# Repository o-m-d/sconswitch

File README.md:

# Serial Controlled Switch

## Device description
Device have 32 high voltage open collector outputs, controlled by commands
via RS-232 port. Outputs can be in active or passive state and can drive
relays, solenoids, LEDs, opto triacs etc.
Active state - output transistor open, passive state - output transistor
closed.

Device can be used in power control, lighting or any other suitable
applications.

Device connects to controlled system via 40-wire ribbon cable and to
controlling host via DE9 connector.

Device IS NOT realtime and may not used in time-sensitive applications,
e.g. CNC.

Device built on microcontroller ATmega8515-16 in TQFP44 package and
drivers ULN2803A in SOIC-18 package.

In firmware part used [KonstantinChizhov/Mcucpp library] (https://github.com/KonstantinChizhov/Mcucpp)
and [Peter Fleury UART library] (http://homepage.hispeed.ch/peterfleury/avr-software.html).
Firmware compiled by avr-gcc-4.8, pcb designed in KiCAD-4.0.1.

## Supported commands
<pre>
a N|a   - Active output number N (or all)
p N|a   - Passive output number N (or all)
t N D   - Toggle output N for D (1-255) seconds, press s for stop during 
          countdown
n NAME  - Output name, set to NAME or unset if empty given
s       - Show output status
h or ?  - Show this help
</pre>

Output status saved automatically to EEPROM with Active or Passive commands
and restored when power-up.
Commands are not case sensitive. Command line are not editable.

Outputs have numbers from 0 to 31. Toggle means temporary inversion of
output state.

[Demo video](https://youtu.be/6nN7ayRqDR0)

## Electrical characteristics
<pre>
Supply voltage: 9-15V
Supply current: 25mA at 10V
Max voltage on closed output: 50V
Max current via one open output: 500mA
Max total current via all open outputs: 4A (125mA per output and 2x2A per
two ground wires in ribbon cable)
</pre>

Characteristics depend on applied components.

## RS-232 mode
9600 8N1

## Design Recommendations
* Use short as possible ribbon cable.
* Use only 40-wire ribbon cable, not 80-wire UDMA cable.
* ULN2803 have built-in surge protection diodes for inductive load, but
better use discrete diodes, placed as close as possible to coil.

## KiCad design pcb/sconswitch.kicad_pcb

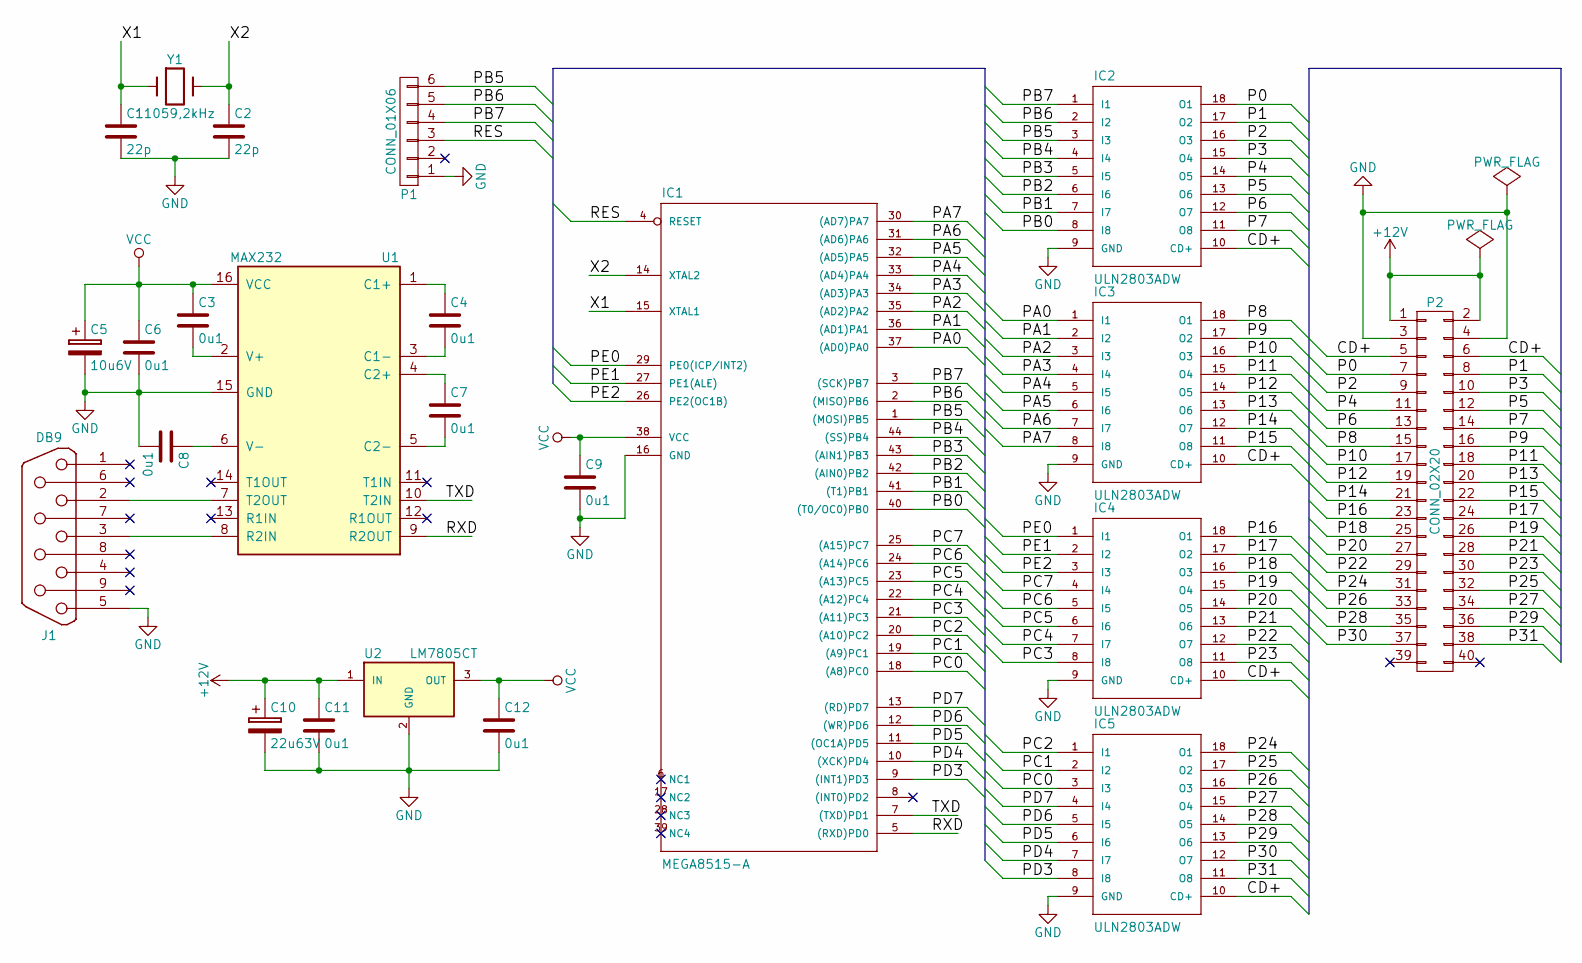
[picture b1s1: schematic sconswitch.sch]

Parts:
C1, C2: 22p; C_0603
C3, C4, C6, C7, C8, C9, C11, C12: 0u1; C_0603
C5: 10u6V; C_Radial_D5_L6_P2.5
C10: 22u63V; C_Radial_D10_L13_P5
IC1: MEGA8515-A; TQFP-44_10x10mm_Pitch0.8mm
IC2, IC3, IC4, IC5: ULN2803ADW; SOIC-18_7.5x11.6mm_Pitch1.27mm
J1: DB9; DB9FC
P1: CONN_01X06; Pin_Header_Straight_1x06
P2: CONN_02X20; Pin_Header_Straight_2x20
U1: MAX232; SO-16-N
U2: LM7805CT; TO-220_Horizontal_LargePads
Y1: 11059,2kHz; Crystal_HC49-U_Horizontal_Typ1

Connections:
+12V: C10.1, C11.1, P2.1, P2.2, U2.1 (IN)
/CD+: IC2.10 (CD+), IC3.10 (CD+), IC4.10 (CD+), IC5.10 (CD+), P2.5, P2.6
/P0: IC2.18 (O1), P2.7
/P1: IC2.17 (O2), P2.8
/P2: IC2.16 (O3), P2.9
/P3: IC2.15 (O4), P2.10
/P4: IC2.14 (O5), P2.11
/P5: IC2.13 (O6), P2.12
/P6: IC2.12 (O7), P2.13
/P7: IC2.11 (O8), P2.14
/P8: IC3.18 (O1), P2.15
/P9: IC3.17 (O2), P2.16
/P10: IC3.16 (O3), P2.17
/P11: IC3.15 (O4), P2.18
/P12: IC3.14 (O5), P2.19
/P13: IC3.13 (O6), P2.20
/P14: IC3.12 (O7), P2.21
/P15: IC3.11 (O8), P2.22
/P16: IC4.18 (O1), P2.23
/P17: IC4.17 (O2), P2.24
/P18: IC4.16 (O3), P2.25
/P19: IC4.15 (O4), P2.26
/P20: IC4.14 (O5), P2.27
/P21: IC4.13 (O6), P2.28
/P22: IC4.12 (O7), P2.29
/P23: IC4.11 (O8), P2.30
/P24: IC5.18 (O1), P2.31
/P25: IC5.17 (O2), P2.32
/P26: IC5.16 (O3), P2.33
/P27: IC5.15 (O4), P2.34
/P28: IC5.14 (O5), P2.35
/P29: IC5.13 (O6), P2.36
/P30: IC5.12 (O7), P2.37
/P31: IC5.11 (O8), P2.38
/PA0: IC1.37 ((AD0)PA0), IC3.1 (I1)
/PA1: IC1.36 ((AD1)PA1), IC3.2 (I2)
/PA2: IC1.35 ((AD2)PA2), IC3.3 (I3)
/PA3: IC1.34 ((AD3)PA3), IC3.4 (I4)
/PA4: IC1.33 ((AD4)PA4), IC3.5 (I5)
/PA5: IC1.32 ((AD5)PA5), IC3.6 (I6)
/PA6: IC1.31 ((AD6)PA6), IC3.7 (I7)
/PA7: IC1.30 ((AD7)PA7), IC3.8 (I8)
/PB0: IC1.40 ((T0/OC0)PB0), IC2.8 (I8)
/PB1: IC1.41 ((T1)PB1), IC2.7 (I7)
/PB2: IC1.42 ((AIN0)PB2), IC2.6 (I6)
/PB3: IC1.43 ((AIN1)PB3), IC2.5 (I5)
/PB4: IC1.44 ((SS)PB4), IC2.4 (I4)
/PB5: IC1.1 ((MOSI)PB5), IC2.3 (I3), P1.6
/PB6: IC1.2 ((MISO)PB6), IC2.2 (I2), P1.5
/PB7: IC1.3 ((SCK)PB7), IC2.1 (I1), P1.4
/PC0: IC1.18 ((A8)PC0), IC5.3 (I3)
/PC1: IC1.19 ((A9)PC1), IC5.2 (I2)
/PC2: IC1.20 ((A10)PC2), IC5.1 (I1)
/PC3: IC1.21 ((A11)PC3), IC4.8 (I8)
/PC4: IC1.22 ((A12)PC4), IC4.7 (I7)
/PC5: IC1.23 ((A13)PC5), IC4.6 (I6)
/PC6: IC1.24 ((A14)PC6), IC4.5 (I5)
/PC7: IC1.25 ((A15)PC7), IC4.4 (I4)
/PD3: IC1.9 ((INT1)PD3), IC5.8 (I8)
/PD4: IC1.10 ((XCK)PD4), IC5.7 (I7)
/PD5: IC1.11 ((OC1A)PD5), IC5.6 (I6)
/PD6: IC1.12 ((WR)PD6), IC5.5 (I5)
/PD7: IC1.13 ((RD)PD7), IC5.4 (I4)
/PE0: IC1.29 (PE0(ICP/INT2)), IC4.1 (I1)
/PE1: IC1.27 (PE1(ALE)), IC4.2 (I2)
/PE2: IC1.26 (PE2(OC1B)), IC4.3 (I3)
/RES: IC1.4 (RESET), P1.3
/RXD: IC1.5 ((RXD)PD0), U1.9 (R2OUT)
/TXD: IC1.7 ((TXD)PD1), U1.10 (T2IN)
/X1: C1.1, IC1.15 (XTAL1), Y1.1
/X2: C2.1, IC1.14 (XTAL2), Y1.2
GND: C1.2, C2.2, C5.2, C6.2, C8.2, C9.2, C10.2, C11.2, C12.2, IC1.16 (GND), IC2.9 (GND), IC3.9 (GND), IC4.9 (GND), IC5.9 (GND), J1.5, P1.1, P2.3, P2.4, U1.15 (GND), U2.2 (GND)
unnamed: C3.2, U1.2 (V+)
unnamed: C4.1, U1.1 (C1+)
unnamed: C4.2, U1.3 (C1-)
unnamed: C7.1, U1.4 (C2+)
unnamed: C7.2, U1.5 (C2-)
unnamed: C8.1, U1.6 (V-)
unnamed: J1.2, U1.7 (T2OUT)
unnamed: J1.3, U1.8 (R2IN)
VCC: C3.1, C5.1, C6.1, C9.1, C12.1, IC1.38 (VCC), U1.16 (VCC), U2.3 (OUT)

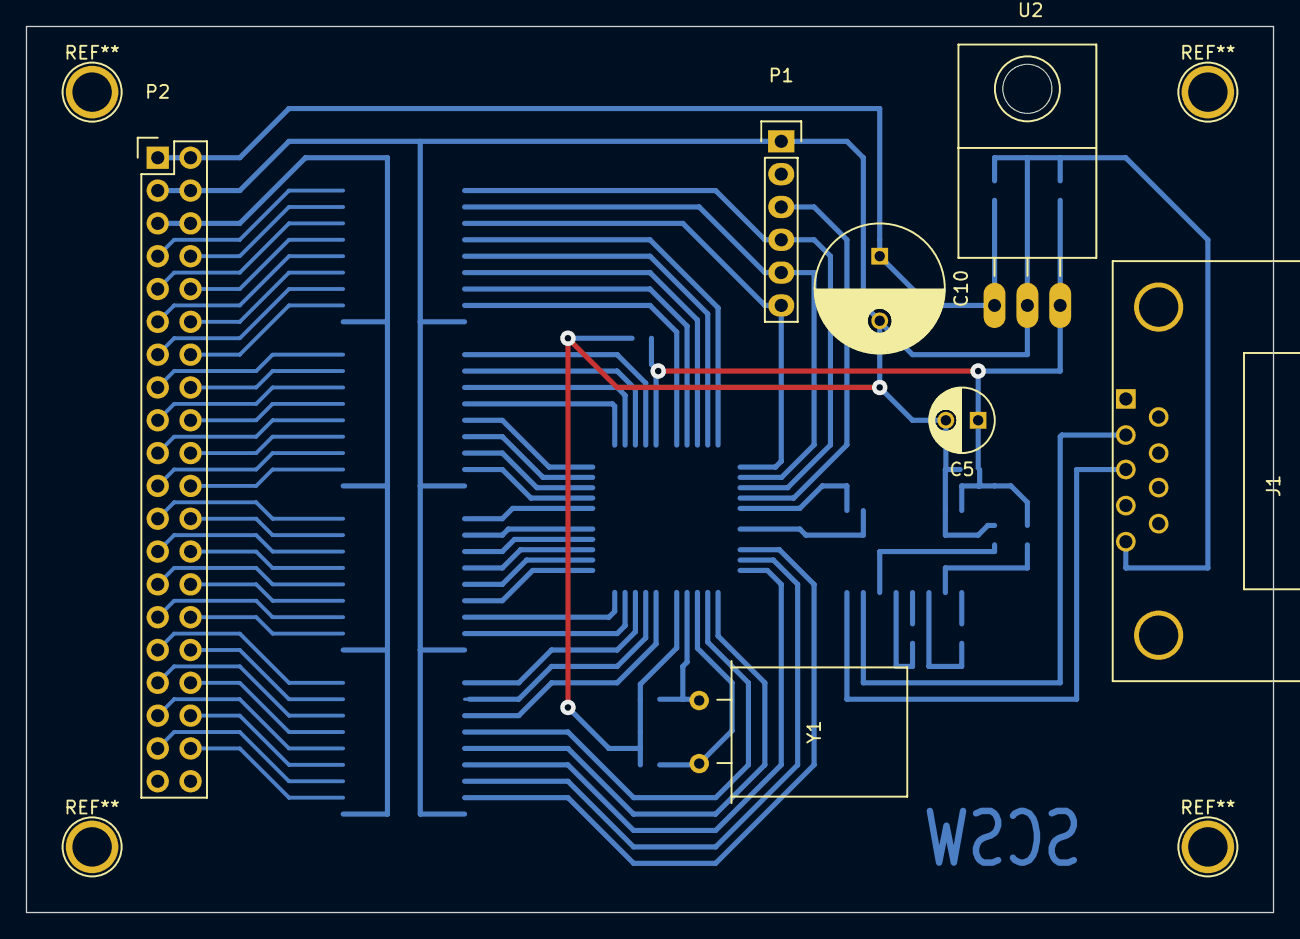
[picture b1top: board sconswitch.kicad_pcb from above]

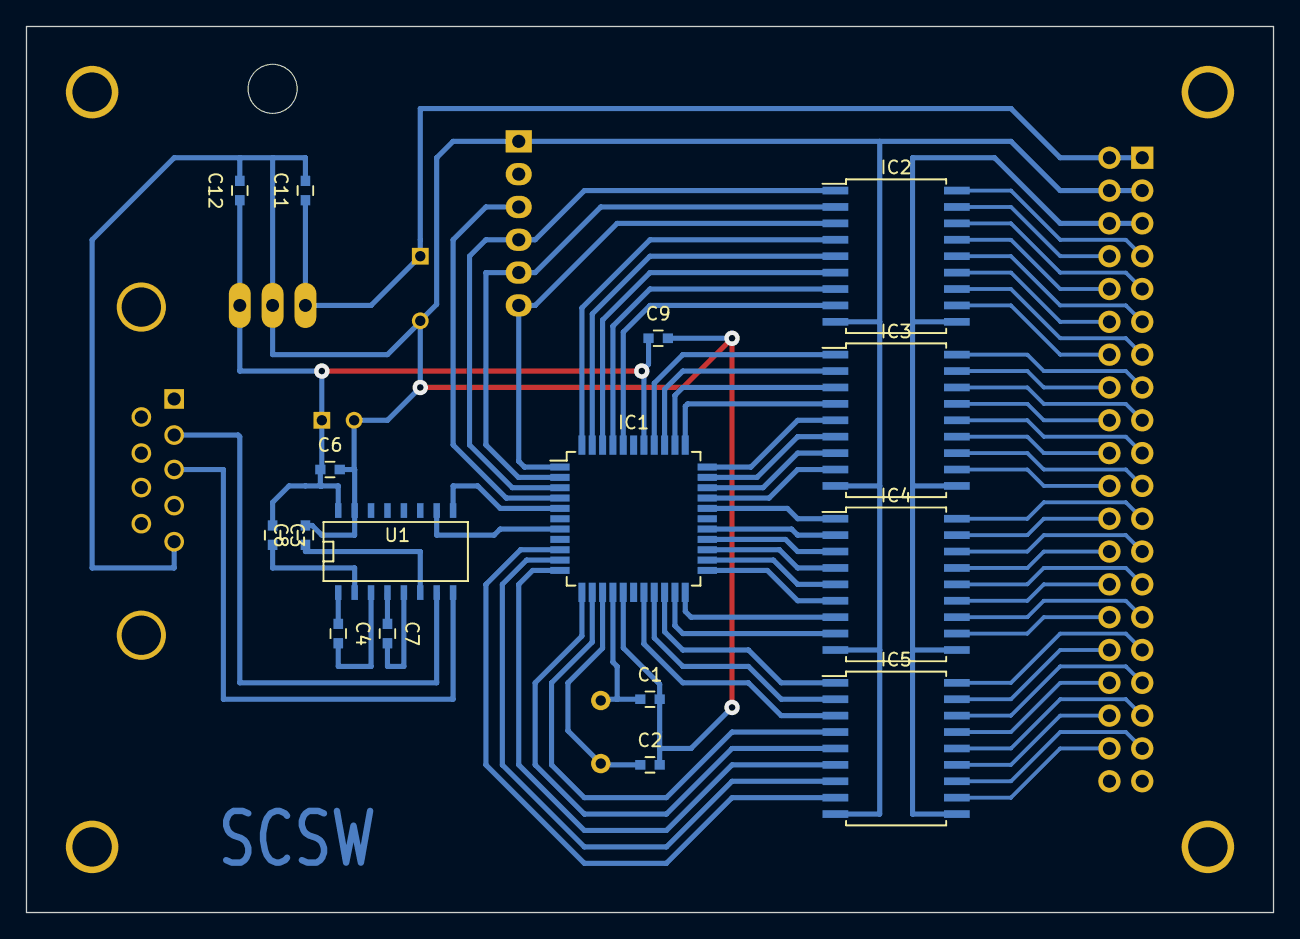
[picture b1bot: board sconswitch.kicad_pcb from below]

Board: 2 copper layers, 96.5 x 68.6 mm, 23 parts (16 on the bottom side), 81 nets.

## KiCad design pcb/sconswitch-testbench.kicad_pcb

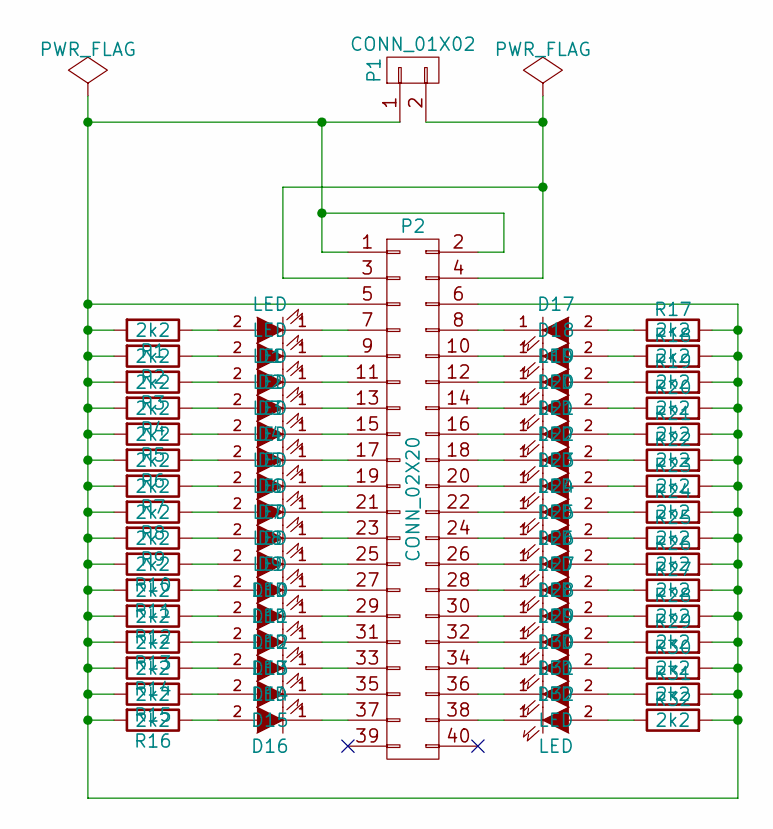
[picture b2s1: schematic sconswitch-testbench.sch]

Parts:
D1, D2, D3, D4, D5, D6, D7, D8, D9, D10, D11, D12, D13, D14, D15, D16, D17, D18, D19, D20, D21, D22, D23, D24, D25, D26, D27, D28, D29, D30, D31, D32: LED; LED_0805
P1: CONN_01X02; TerminalBlock_Pheonix_MKDS1.5-2pol
P2: CONN_02X20; Pin_Header_Straight_2x20
R1, R2, R3, R4, R5, R6, R7, R8, R9, R10, R11, R12, R13, R14, R15, R16, R17, R18, R19, R20, R21, R22, R23, R24, R25, R26, R27, R28, R29, R30, R31, R32: 2k2; R_0805

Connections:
unnamed: D1.1 (K), P2.7
unnamed: D1.2 (A), R1.1
unnamed: D2.1 (K), P2.9
unnamed: D2.2 (A), R2.1
unnamed: D3.1 (K), P2.11
unnamed: D3.2 (A), R3.1
unnamed: D4.1 (K), P2.13
unnamed: D4.2 (A), R4.1
unnamed: D5.1 (K), P2.15
unnamed: D5.2 (A), R5.1
unnamed: D6.1 (K), P2.17
unnamed: D6.2 (A), R6.1
unnamed: D7.1 (K), P2.19
unnamed: D7.2 (A), R7.1
unnamed: D8.1 (K), P2.21
unnamed: D8.2 (A), R8.1
unnamed: D9.1 (K), P2.23
unnamed: D9.2 (A), R9.1
unnamed: D10.1 (K), P2.25
unnamed: D10.2 (A), R10.1
unnamed: D11.1 (K), P2.27
unnamed: D11.2 (A), R11.1
unnamed: D12.1 (K), P2.29
unnamed: D12.2 (A), R12.1
unnamed: D13.1 (K), P2.31
unnamed: D13.2 (A), R13.1
unnamed: D14.1 (K), P2.33
unnamed: D14.2 (A), R14.1
unnamed: D15.1 (K), P2.35
unnamed: D15.2 (A), R15.1
unnamed: D16.1 (K), P2.37
unnamed: D16.2 (A), R16.1
unnamed: D17.1 (K), P2.8
unnamed: D17.2 (A), R17.1
unnamed: D18.1 (K), P2.10
unnamed: D18.2 (A), R18.1
unnamed: D19.1 (K), P2.12
unnamed: D19.2 (A), R19.1
unnamed: D20.1 (K), P2.14
unnamed: D20.2 (A), R20.1
unnamed: D21.1 (K), P2.16
unnamed: D21.2 (A), R21.1
unnamed: D22.1 (K), P2.18
unnamed: D22.2 (A), R22.1
unnamed: D23.1 (K), P2.20
unnamed: D23.2 (A), R23.1
unnamed: D24.1 (K), P2.22
unnamed: D24.2 (A), R24.1
unnamed: D25.1 (K), P2.24
unnamed: D25.2 (A), R25.1
unnamed: D26.1 (K), P2.26
unnamed: D26.2 (A), R26.1
unnamed: D27.1 (K), P2.28
unnamed: D27.2 (A), R27.1
unnamed: D28.1 (K), P2.30
unnamed: D28.2 (A), R28.1
unnamed: D29.1 (K), P2.32
unnamed: D29.2 (A), R29.1
unnamed: D30.1 (K), P2.34
unnamed: D30.2 (A), R30.1
unnamed: D31.1 (K), P2.36
unnamed: D31.2 (A), R31.1
unnamed: D32.1 (K), P2.38
unnamed: D32.2 (A), R32.1
unnamed: P1.1, P2.1, P2.2, P2.5, P2.6, R1.2, R2.2, R3.2, R4.2, R5.2, R6.2, R7.2, R8.2, R9.2, R10.2, R11.2, R12.2, R13.2, R14.2, R15.2, R16.2, R17.2, R18.2, R19.2, R20.2, R21.2, R22.2, R23.2, R24.2, R25.2, R26.2, R27.2, R28.2, R29.2, R30.2, R31.2, R32.2
unnamed: P1.2, P2.3, P2.4

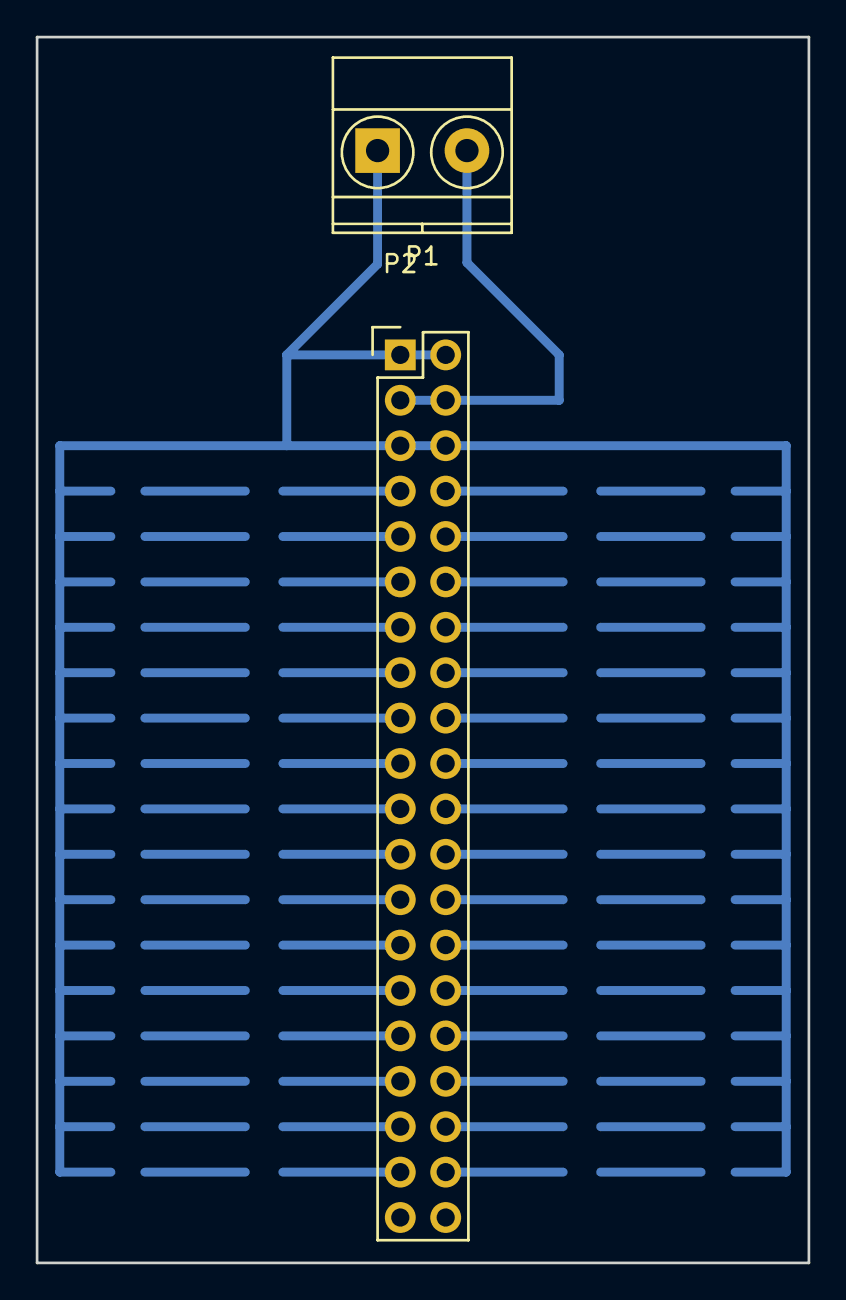
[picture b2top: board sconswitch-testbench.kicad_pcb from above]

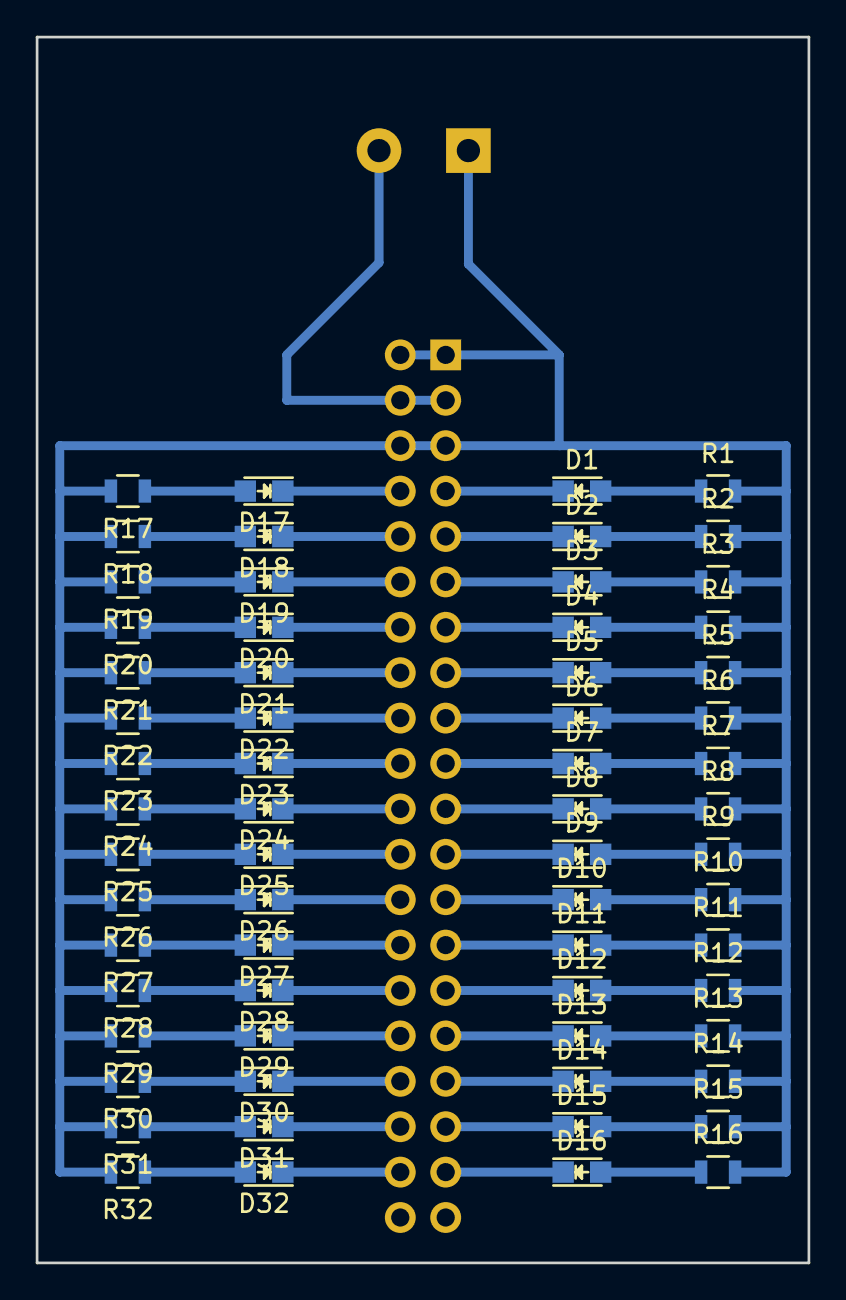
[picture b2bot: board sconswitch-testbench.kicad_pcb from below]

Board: 2 copper layers, 43.2 x 68.6 mm, 66 parts (64 on the bottom side), 66 nets.

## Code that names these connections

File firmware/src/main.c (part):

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
using namespace Mcucpp::IO;

typedef PinList <Pb7, Pb6, Pb5, Pb4, Pb3, Pb2, Pb1, Pb0, Pa0, Pa1, Pa2, Pa3, Pa4, Pa5, Pa6, Pa7, Pe0, Pe1, Pe2, Pc7, Pc6, Pc5, Pc4, Pc3, Pc2, Pc1, Pc0, Pd7, Pd6, Pd5, Pd4, Pd3> mainport;

const int8_t mainport_width = mainport::PinListProperties::Length - 1;
uint32_t mainport_data;
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
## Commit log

2016-03-20 Fix README.md
